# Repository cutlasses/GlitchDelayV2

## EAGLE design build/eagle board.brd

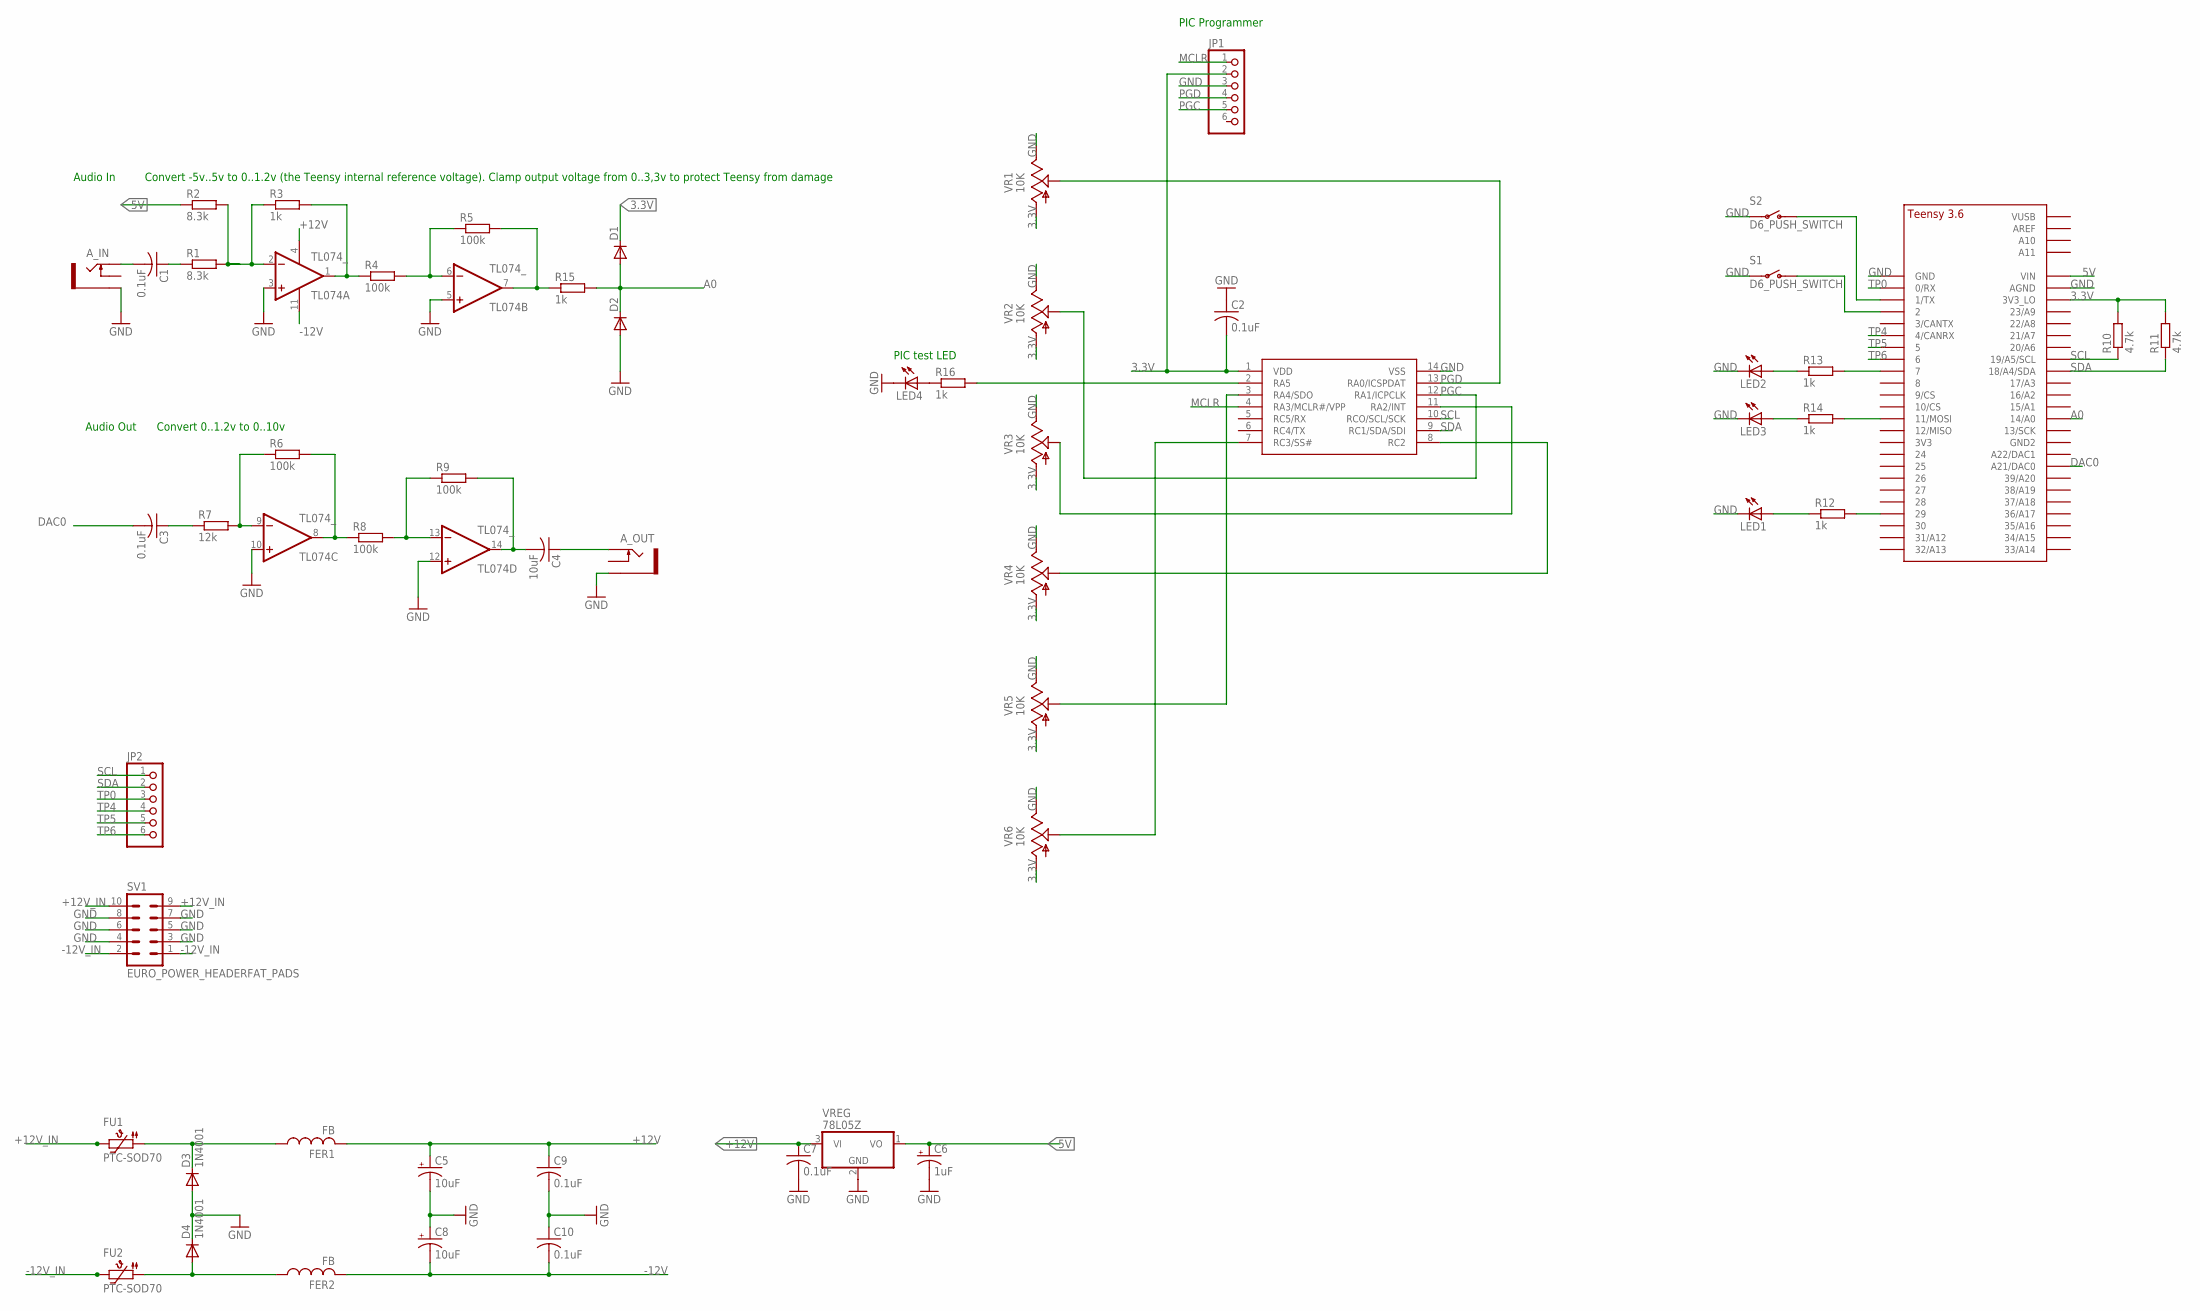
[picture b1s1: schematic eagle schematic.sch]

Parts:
A_IN: THONKICONNNEW; WQP-PJ301M-12_JACK
A_OUT: THONKICONNNEW; WQP-PJ301M-12_JACK
C1, C2, C3, C7, C9, C10: 0.1uF; C025-030X050
C4: 10uF; C025-030X050
C5, C8: 10uF; E2,5-6E
C6: 1uF; E2,5-7
D1, D2: SMALL_DIODEDO35-7; DO35-7
D3, D4: 1N4001; DO41-10
FER1, FER2: FB
FU1, FU2: PTC-SOD70; SOD70
JP1, JP2: PINHD-1X6; 1X06
LED1, LED2, LED3, LED4: LED3MM
PIC: PIC16F1825DIL14; DIL14
R1, R2: 8.3k; 7MM_RESISTOR
R3, R12, R13, R14, R15, R16: 1k; 7MM_RESISTOR
R4, R5, R6, R8, R9: 100k; 7MM_RESISTOR
R7: 12k; 7MM_RESISTOR
R10, R11: 4.7k; 7MM_RESISTOR
S1, S2: D6_PUSH_SWITCH
SV1: EURO_POWER_HEADERFAT_PADS; EURO_PWR_HEADER_FAT
TL074: TL074_; DIL14
U$1: TEENSY_3.5/3.6_BASIC
VR1, VR2, VR3, VR4, VR5, VR6: 10K; 9MM_SNAP-IN_POT
VREG: 78L05Z; TO92

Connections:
3.3V: C2.2, D1.C, JP1.2, PIC.1 (VDD), R10.2, R11.2, U$1.3V3_LO, VR1.1 (A), VR2.1 (A), VR3.1 (A), VR4.1 (A), VR5.1 (A), VR6.1 (A)
5V: C6.+, R2.1, U$1.VIN, VREG.1 (VO)
+12V: C5.+, C7.1, C9.1, FER1.P$2 (2), TL074.4 (V+), VREG.3 (VI)
+12V_IN: FU1.2, SV1.9, SV1.10
-12V: C8.-, C10.2, FER2.P$2 (2), TL074.11 (V-)
-12V_IN: FU2.2, SV1.1, SV1.2
A0: D1.A, D2.C, R15.2, U$1.14/A0
DAC0: C3.2, U$1.21/DAC0 (A21/DAC0)
GND: A_IN.P$3_SLEEVE (SLEEVE), A_OUT.P$3_SLEEVE (SLEEVE), C2.1, C5.-, C6.-, C7.2, C8.+, C9.2, C10.1, D2.A, D3.A, D4.C, JP1.3, LED1.K (C), LED2.K (C), LED3.K (C), LED4.K (C), PIC.14 (VSS), S1.P$3, S1.P$4, S2.P$3, S2.P$4, SV1.3, SV1.4, SV1.5, SV1.6, SV1.7, SV1.8, TL074.3 (+IN), TL074.5 (+IN), TL074.10 (+IN), TL074.12 (+IN), U$1.AGND, U$1.GND, VR1.3 (E), VR2.3 (E), VR3.3 (E), VR4.3 (E), VR5.3 (E), VR6.3 (E), VREG.2 (GND)
MCLR: JP1.1, PIC.4 (RA3/MCLR#/VPP)
unnamed: LED4.A, R16.1
unnamed: A_IN.P$1_TIP (TIP), C1.2
unnamed: R1.2, R2.2, R3.1, TL074.2 (-IN)
unnamed: R3.2, R4.1, TL074.1 (OUT)
unnamed: PIC.2 (RA5), R16.2
unnamed: R4.2, R5.1, TL074.6 (-IN)
unnamed: C1.1, R1.1
unnamed: R5.2, R15.1, TL074.7 (OUT)
unnamed: LED1.A, R12.1
unnamed: PIC.11 (RA2/INT), VR3.2 (S)
unnamed: PIC.8 (RC2), VR4.2 (S)
unnamed: PIC.3 (RA4/SDO), VR5.2 (S)
unnamed: C3.1, R7.1
unnamed: R6.1, R7.2, TL074.9 (-IN)
unnamed: PIC.7 (RC3/SS#), VR6.2 (S)
unnamed: R6.2, R8.1, TL074.8 (OUT)
unnamed: R12.2, U$1.29
unnamed: R8.2, R9.1, TL074.13 (-IN)
unnamed: LED2.A, R13.1
unnamed: S1.P$1 (O), S1.P$2 (O), U$1.2
unnamed: C4.2, R9.2, TL074.14 (OUT)
unnamed: A_OUT.P$1_TIP (TIP), C4.1
unnamed: LED3.A, R14.1
unnamed: S2.P$1 (O), S2.P$2 (O), U$1.1/TX
unnamed: R13.2, U$1.7
unnamed: R14.2, U$1.11/MOSI
unnamed: D3.C, FER1.P$1 (1), FU1.1
unnamed: D4.A, FER2.P$1 (1), FU2.1
PGC: JP1.5, PIC.12 (RA1/ICPCLK), VR2.2 (S)
PGD: JP1.4, PIC.13 (RA0/ICSPDAT), VR1.2 (S)
SCL: JP2.1, PIC.10 (RCO/SCL/SCK), R10.1, U$1.19/A5/SCL
SDA: JP2.2, PIC.9 (RC1/SDA/SDI), R11.1, U$1.18/A4/SDA
TP0: JP2.3, U$1.0/RX
TP4: JP2.4, U$1.4/CANRX
TP5: JP2.5, U$1.5
TP6: JP2.6, U$1.6

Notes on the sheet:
Audio In
Audio Out
Convert -5v..5v to 0..1.2v (the Teensy internal reference voltage). Clamp output voltage from 0..3,3v to protect Teensy from damage
Convert 0..1.2v to 0..10v
PIC Programmer
PIC test LED

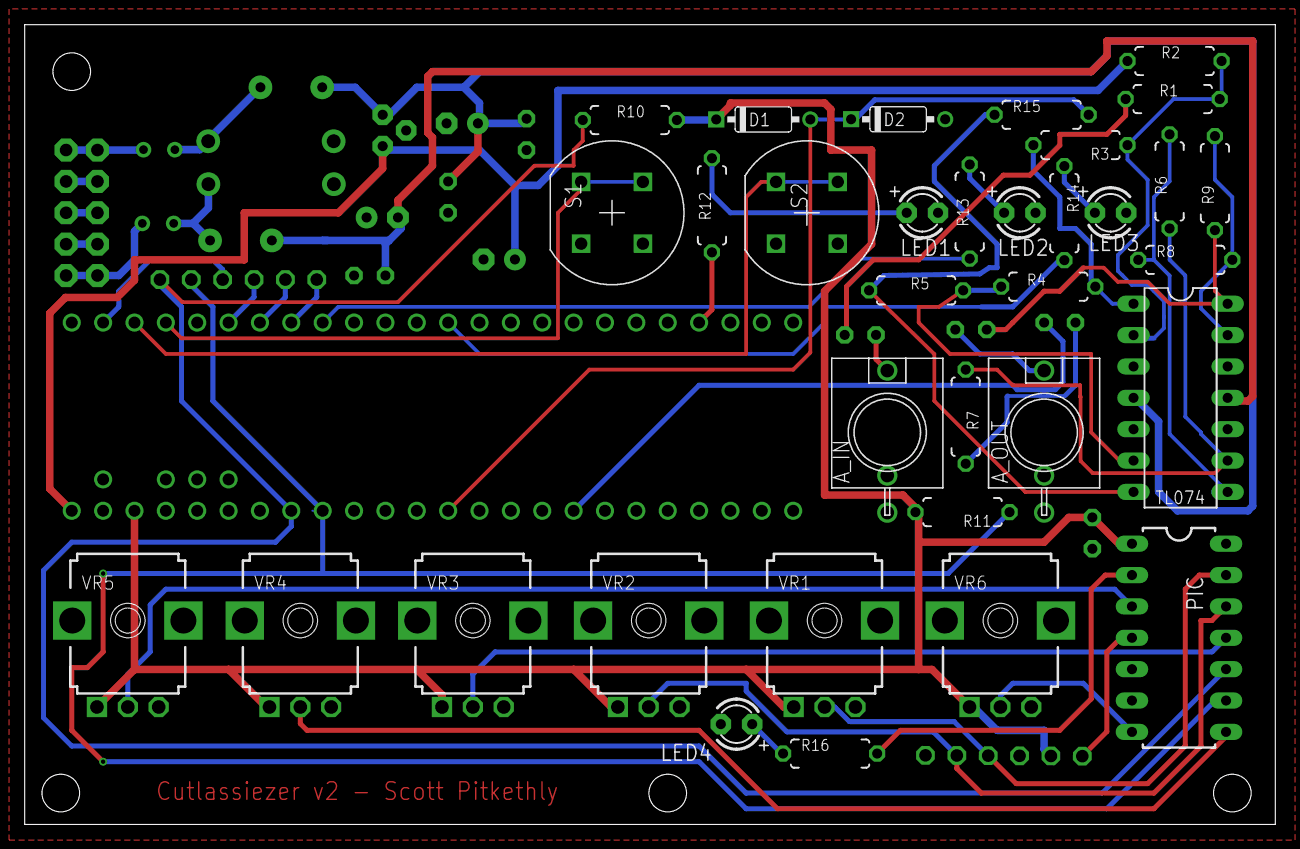
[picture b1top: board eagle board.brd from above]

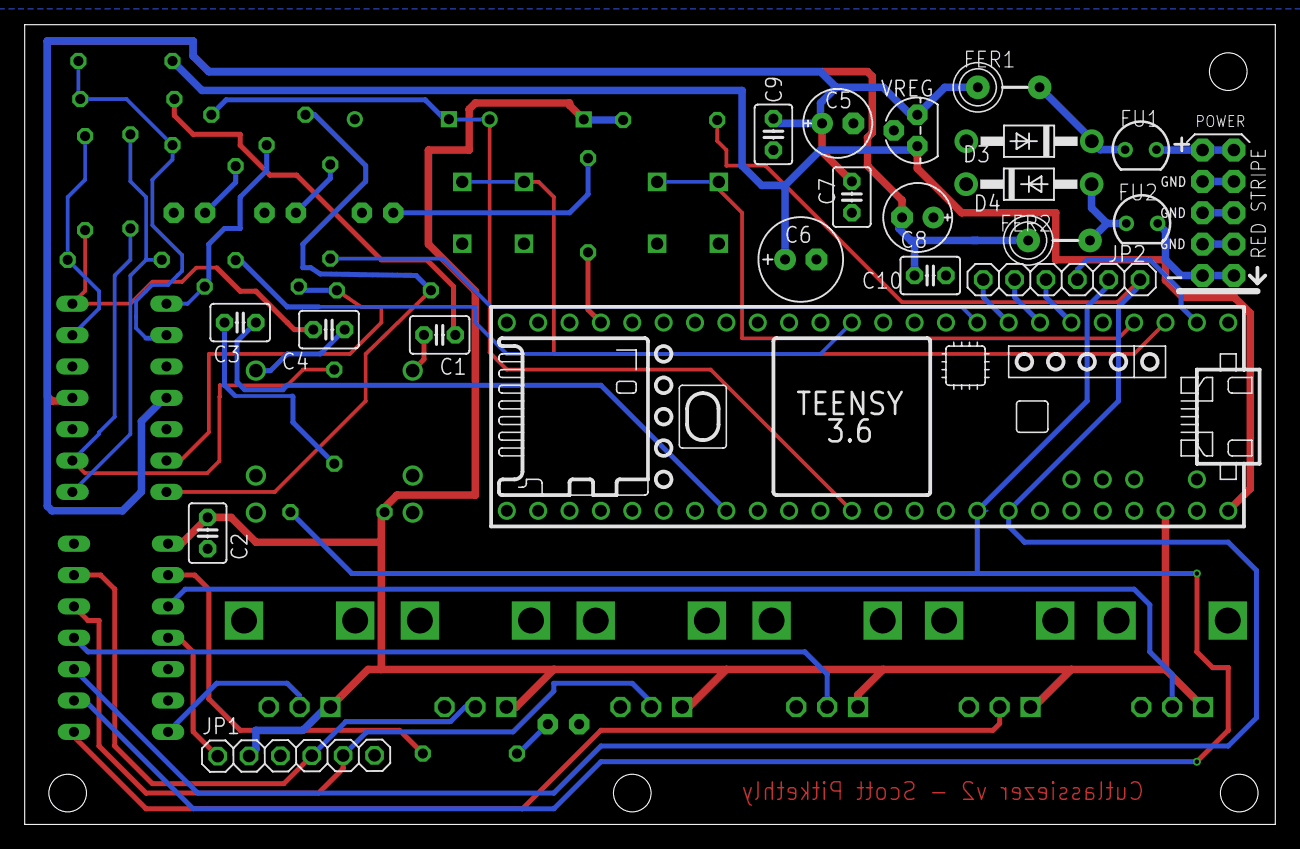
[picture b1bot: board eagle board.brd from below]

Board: 2 copper layers, 101.3 x 64.8 mm, 55 parts (21 on the bottom side), 46 nets.

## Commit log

2017-08-06 Initial commit
    Currently just a copy of V1
2017-08-06 File rename
2017-08-06 Introducing I2C_DIAL
2017-08-07 Fixing LEDs
2017-08-08 DIAL refactoring
2017-08-08 Pot now read correctly!
    Arduino supports lambdas!
2017-08-08 Audio working with new board!
    A bit noisy for some reason
2017-08-10 Stand alone audio working
2017-08-12 Updated PIC code
    PIC now reads only connected pots, and in order they are mounted on PCB.
2017-08-12 Hooking up octave pots
2017-10-09 Implementing TeensyJuce
2017-12-09 Lots of changes (from plug in version)
    Reverse head added
    Freeze mode added
    Dials remapped (interface no longer exposes dials, just values, to make
    it easier to remap)
2018-02-21 Adding support for Teensy based interface (instead of PIC)
    Using ADC library to allow all pots to connect to Teensy instead of PIC
2018-02-21 Turning on define which matches attached build docs
2018-02-21 Compile fix
2018-02-22 Adding ADC support
    Pots can now be read on Teensy
2018-04-24 Create dummy
2018-05-15 Fixes for new PCB
2018-05-15 Setting voltage reference
2018-06-25 Adding schematic for top board
2018-06-25 Adding Gerbers
2018-07-22 More funnctionality
    Adding push and turn for
    -head mix
    -feedback
2018-07-29 Using remote I2C interface for CV control
    Adding CV_DIAL which wraps together the on-board pot and off-board CV
2018-07-29 Adding CV control
2021-08-22 Removing audio adaptor defines
    Conflict with latest teensy libs?
